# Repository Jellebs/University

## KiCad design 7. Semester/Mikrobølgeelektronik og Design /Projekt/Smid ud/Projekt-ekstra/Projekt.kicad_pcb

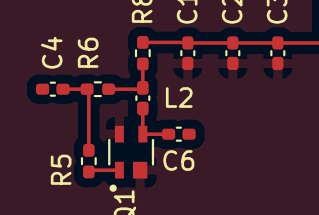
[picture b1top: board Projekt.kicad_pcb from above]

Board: 2 copper layers, 10 parts (0 on the bottom side), 6 nets.

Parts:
C1: 100p; C_0402_1005Metric_Pad0.74x0.62mm_HandSolder
C2: 100n; C_0402_1005Metric_Pad0.74x0.62mm_HandSolder
C3: 1u; C_0402_1005Metric_Pad0.74x0.62mm_HandSolder
C4, C6: C; C_0402_1005Metric_Pad0.74x0.62mm_HandSolder
L2: 15n; L_0402_1005Metric_Pad0.77x0.64mm_HandSolder
Q1: SOT130P210X100-4N
R5: 4; R_0402_1005Metric_Pad0.72x0.64mm_HandSolder
R6: 9500; R_0402_1005Metric_Pad0.72x0.64mm_HandSolder
R8: 75; R_0402_1005Metric_Pad0.72x0.64mm_HandSolder

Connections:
GND: C1.1, C2.1, C3.1, Q1.2, Q1.4
unnamed: C4.2, R5.2, R6.1
unnamed: C6.1, L2.2, Q1.3
unnamed: L2.1, R6.2, R8.1
unnamed: Q1.1, R5.1
VDD: C1.2, C2.2, C3.2, R8.2

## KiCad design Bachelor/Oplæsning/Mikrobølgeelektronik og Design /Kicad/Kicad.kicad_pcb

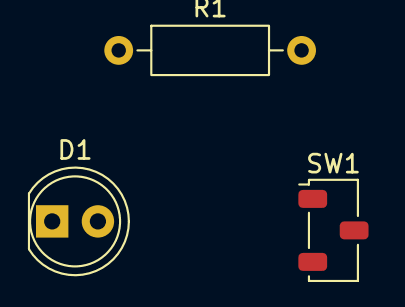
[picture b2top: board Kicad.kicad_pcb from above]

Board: 2 copper layers, 3 parts (0 on the bottom side), 3 nets, no tracks yet.

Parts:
D1: 0.7; LED_D5.0mm
R1: 140; R_Axial_DIN0207_L6.3mm_D2.5mm_P10.16mm_Horizontal
SW1: SW_Nidec_CAS-120A1; Nidec_Copal_CAS-120A

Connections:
GND: R1.2, SW1.3 (A)
unnamed: D1.2 (A), SW1.1 (C)
unnamed: D1.1 (K), R1.1

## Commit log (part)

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2023-02-21 Initialized the repository, added gitignore
2023-02-21 Added ignores to the gitignore
2023-02-21 Got gitignore to work. Now pushing it to github
2023-03-03 Uge 9 klaret
2023-03-10 Færdig med uge 10
2023-03-24 Uge 8 klaret
2023-03-24 Uge 8 klaret, nu også med elektriske kredsløb
2023-04-21 Slutningen på uge 11)
2023-05-19 Færdig med den sidste uge af dette semester, den 14. uge, i uge 20
2023-06-09 Færdig med 3 uge af læse ferien, Analog eksamen kommer om 4 dage
2023-06-27 Faerdig med at laese op, nu mangler sidste jeg sidste eksamen i morgen
2024-03-05 1.5 måned inde i 4 semester
2024-05-31 Haaber alt er fikset nu
2024-05-31 Nu er jeg opdateret
2024-06-26 Faerdig med 4 semester, nu der sommerferie!
2024-11-27 Nu lakker jeg mod enden af 5. semester
2025-01-07 Faerdig med foerste eksamen til vinter 2024
2025-01-07 Faerdig med foerste eksamen af vinter 2024
2025-02-27 Første opdatering fra 6. semester, hvor den mest af alt står på fysik og signalbehandling
2025-04-29 Paa tide at jeg får gemt mine filer. 6 semester er snart overstået
2025-04-29 Paa tide at jeg får gemt mine filer. 6 semester er snart overstået. Jeg har ændret, at jeg gerne vil have docx filer med, da jeg også arbejder meget i dem nu
2025-05-26 Anden uge i læseferien
2025-05-29 Slut med anden uge, har lavet simulationer til grundlæggende
2025-06-12 Ved at være klar til diskrete tids signal eksamen
2025-08-01 Faerdig med sidste uge inden moderne fysik. I naeste uge gaar det loes
2025-11-19 Bacheloren og 7.semester snart faerdig.
2026-05-04 Tilbage efter orlov, arbejder mig til eksamen i SLML først.
2026-05-08 Færdig med endnu en uge. 2 uger til eksamen i SLML
2026-05-20 Færdig med at læse op til Statistical Learning and Machine Learning, eksamen i morgen
2026-05-31 Starten på en ny uge snart. Mikrobølge eksamen om 3 dage
